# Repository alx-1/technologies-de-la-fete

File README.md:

# technologies-de-la-fete

# The project has moved here : https://gitlab.com/tdlf

ESP32 Ableton Link Midi clock, sensor interface and modular sequencer.

Wiki : https://github.com/alx-1/technologies-de-la-fete/wiki

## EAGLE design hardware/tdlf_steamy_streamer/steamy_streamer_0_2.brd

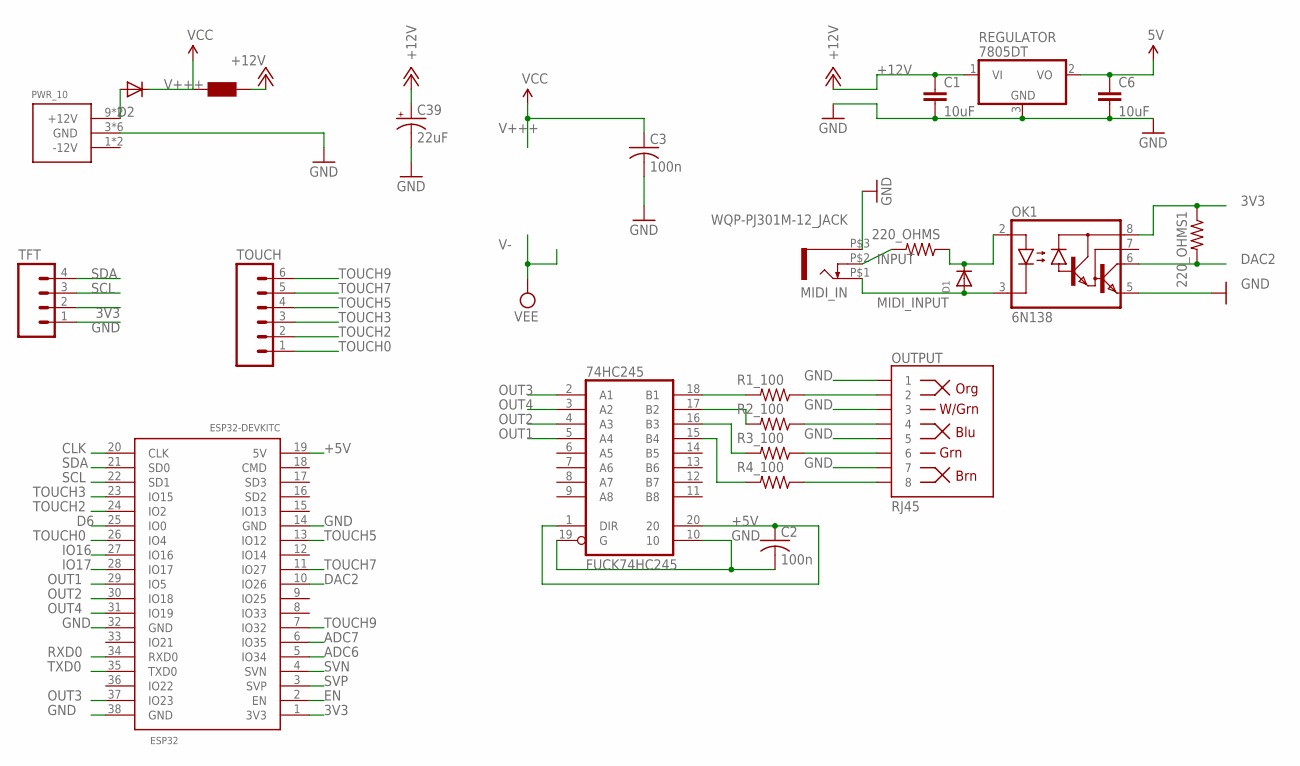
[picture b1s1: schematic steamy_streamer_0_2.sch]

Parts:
74HC245: FUCK74HC245; SO20W
220_OHMS, 220_OHMS1: 1206
C1, C6: 10uF; R1210
C2, C3: 100n; C1206
C39: 22uF; 1206_POL
D1: DIODESMA; SMADIODE
D2: B0450; SOD123
ESP32: ESP32DEVKITC; ESP32-DEVKITC
F1: Würth Electronics 742792664; R0805
MIDI_IN: WQP-PJ301M-12_JACK
OK1: 6N138; DIL08
OUTPUT: RJ45; RJ45-8
PWR_10: POWER_SIMPLE10; POWER_10
R1_100, R2_100, R3_100, R4_100: RESISTOR1206; 1206
REGULATOR: 7805DT; TO252
TFT: M04PTH; 1X04
TOUCH: M06LOCK_LONGPADS; 1X06_LOCK_LONGPADS

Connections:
3V3: 220_OHMS1.1, ESP32.1 (3V3), OK1.8 (VCC), TFT.2
4: OUTPUT.2, R1_100.1
+5V: 74HC245.1 (DIR), 74HC245.20, C2.1, C6.1, ESP32.19 (5V), REGULATOR.2 (VO)
+12V: C1.1, C39.2 (+), F1.1, REGULATOR.1 (VI)
ADC6: ESP32.5 (IO34)
ADC7: ESP32.6 (IO35)
CLK: ESP32.20 (CLK)
D6: ESP32.25 (IO0)
DAC2: 220_OHMS1.2, ESP32.10 (IO26), OK1.6 (VO)
EN: ESP32.2 (EN)
GND: 74HC245.10, 74HC245.19 (G), C1.2, C2.2, C3.2, C6.2, C39.1 (-), ESP32.14 (GND), ESP32.32 (GND), ESP32.38 (GND), MIDI_IN.P$3 (1), OK1.5 (GND), OUTPUT.1, OUTPUT.3, OUTPUT.5, OUTPUT.7, PWR_10.3 (GND), PWR_10.4 (GND), PWR_10.5 (GND), PWR_10.6 (GND), PWR_10.7 (GND), PWR_10.8 (GND), REGULATOR.3 (GND), TFT.1
INPUT: 220_OHMS.2, MIDI_IN.P$2 (3)
IO16: ESP32.27 (IO16)
IO17: ESP32.28 (IO17)
MIDI_INPUT: D1.A, MIDI_IN.P$1 (2), OK1.3 (C)
unnamed: OUTPUT.8, R4_100.1
unnamed: OUTPUT.6, R3_100.1
unnamed: D2.A, PWR_10.9 (+12V), PWR_10.10 (+12V)
unnamed: OUTPUT.4, R2_100.1
unnamed: 220_OHMS.1, D1.C, OK1.2 (A)
unnamed: 74HC245.18 (B1), R1_100.2
unnamed: 74HC245.17 (B2), R2_100.2
unnamed: 74HC245.16 (B3), R3_100.2
unnamed: 74HC245.15 (B4), R4_100.2
OUT1: 74HC245.5 (A4), ESP32.29 (IO5)
OUT2: 74HC245.4 (A3), ESP32.30 (IO18)
OUT3: 74HC245.2 (A1), ESP32.37 (IO23)
OUT4: 74HC245.3 (A2), ESP32.31 (IO19)
RXD0: ESP32.34 (RXD0)
SCL: ESP32.22 (SD1), TFT.3
SDA: ESP32.21 (SD0), TFT.4
SVN: ESP32.4 (SVN)
SVP: ESP32.3 (SVP)
TOUCH0: ESP32.26 (IO4), TOUCH.1
TOUCH2: ESP32.24 (IO2), TOUCH.2
TOUCH3: ESP32.23 (IO15), TOUCH.3
TOUCH5: ESP32.13 (IO12), TOUCH.4
TOUCH7: ESP32.11 (IO27), TOUCH.5
TOUCH9: ESP32.7 (IO32), TOUCH.6
TXD0: ESP32.35 (TXD0)
V+++: C3.1, D2.C, F1.2

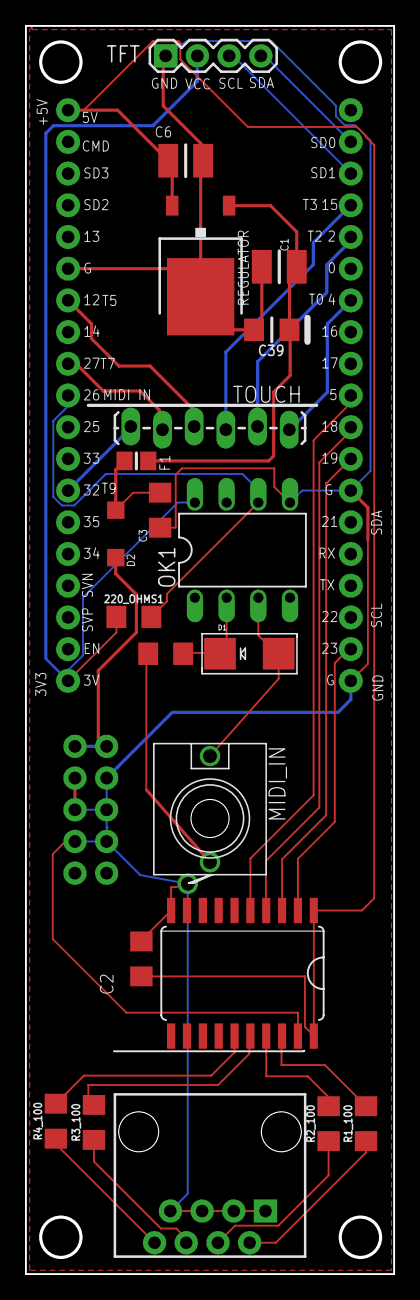
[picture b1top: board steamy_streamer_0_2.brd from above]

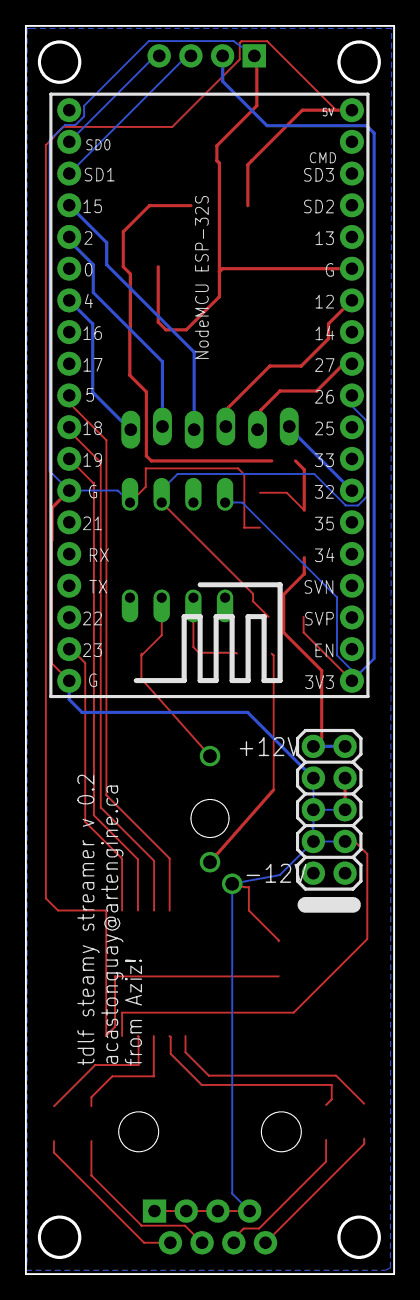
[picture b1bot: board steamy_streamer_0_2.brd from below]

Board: 2 copper layers, 29.5 x 100.0 mm, 23 parts (2 on the bottom side), 30 nets.

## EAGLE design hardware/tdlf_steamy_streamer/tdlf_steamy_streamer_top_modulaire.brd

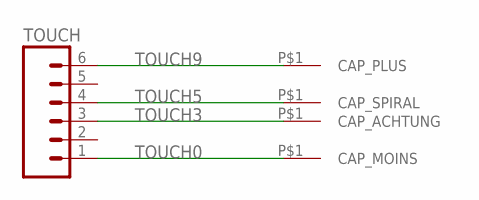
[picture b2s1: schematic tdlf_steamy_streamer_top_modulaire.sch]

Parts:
CAP_PLUS: TDLF_CAP_PLUS
TOUCH: M06SMD-STRAIGHT-COMBO-FEMALE; 1X06_SMD_STRAIGHT_COMBO
U$1: TDLF_CAP_MOINS
U$2: TDLF_CAP_SPIRAL
U$4: TDLF_CAP_ACHTUNG

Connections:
TOUCH0: TOUCH.1, U$1.P$1
TOUCH3: TOUCH.3, U$4.P$1
TOUCH5: TOUCH.4, U$2.P$1
TOUCH9: CAP_PLUS.P$1, TOUCH.6

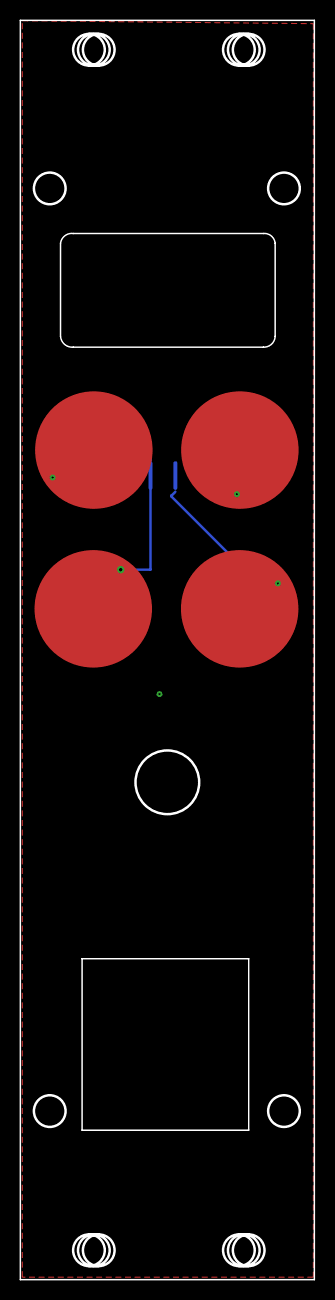
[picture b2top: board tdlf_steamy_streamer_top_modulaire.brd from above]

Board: 2 copper layers, 30.0 x 128.5 mm, 5 parts (1 on the bottom side), 4 nets.

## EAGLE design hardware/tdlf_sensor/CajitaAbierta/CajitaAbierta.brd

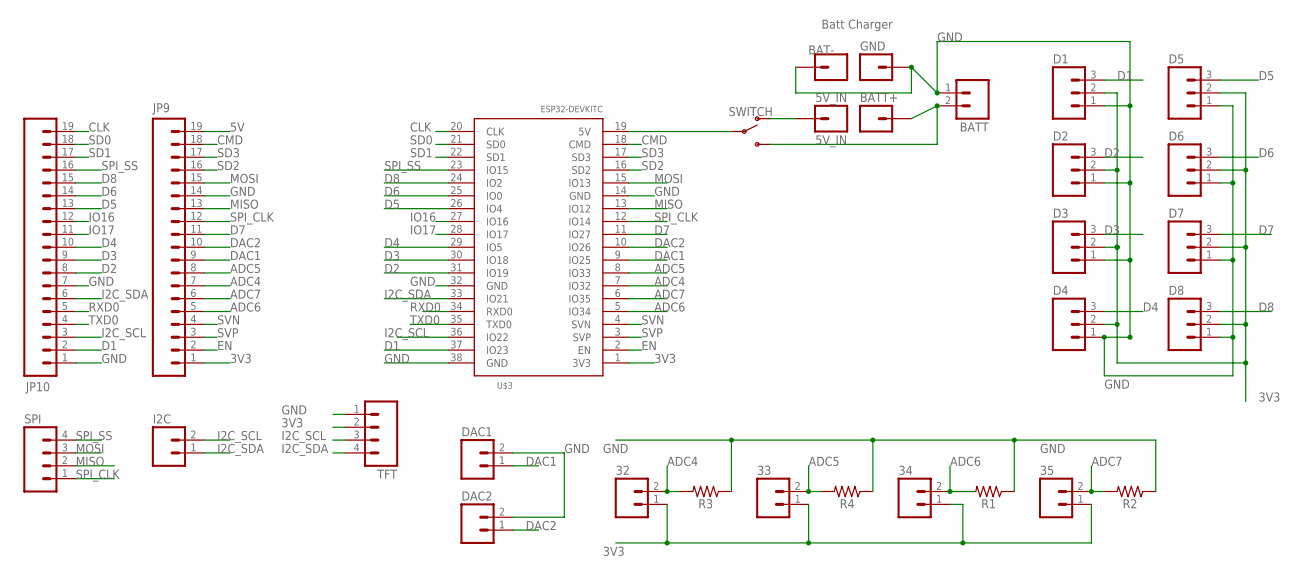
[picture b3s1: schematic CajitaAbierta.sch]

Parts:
5V_IN: 5V_IN; 1X01
32, 33, 34, 35: M02PTH; 1X02
BAT-: M01PTH; 1X01
BATT: M02LOCK_LONGPADS; 1X02_LOCK_LONGPADS
BATT+: M01PTH; 1X01
D1, D2, D3, D4, D5, D6, D7, D8: M03LOCK_LONGPADS; 1X03_LOCK_LONGPADS
DAC1, DAC2: M02PTH; 1X02
GND: Batt Charger; 1X01
I2C: M02PTH; 1X02
JP9, JP10: M191X19; 1X19
R1, R2, R3, R4: 1206
SPI: M04PTH; 1X04
SWITCH: SWITCH-SPDT-SMD-RIGHT-ANGLE; SWITCH_SPST_SMD_A
TFT: M04PTH; 1X04
U$3: ESP32DEVKITC; ESP32-DEVKITC

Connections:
3V3: 32.1, 33.1, 34.1, 35.1, D1.2, D2.2, D3.2, D4.2, D5.2, D6.2, D7.2, D8.2, JP9.1, TFT.2, U$3.1 (3V3)
5V: JP9.19, SWITCH.2, U$3.19 (5V)
5V_IN: 5V_IN.1, SWITCH.1 (O)
ADC4: 32.2, JP9.7, R3.2, U$3.7 (IO32)
ADC5: 33.2, JP9.8, R4.2, U$3.8 (IO33)
ADC6: 34.2, JP9.5, R1.2, U$3.5 (IO34)
ADC7: 35.2, JP9.6, R2.2, U$3.6 (IO35)
BATT+: BATT.2, BATT+.1, SWITCH.3 (S)
CLK: JP10.19, U$3.20 (CLK)
CMD: JP9.18, U$3.18 (CMD)
D1: D1.3, JP10.2, U$3.37 (IO23)
D2: D2.3, JP10.8, U$3.31 (IO19)
D3: D3.3, JP10.9, U$3.30 (IO18)
D4: D4.3, JP10.10, U$3.29 (IO5)
D5: D5.3, JP10.13, U$3.26 (IO4)
D6: D6.3, JP10.14, U$3.25 (IO0)
D7: D7.3, JP9.11, U$3.11 (IO27)
D8: D8.3, JP10.15, U$3.24 (IO2)
DAC1: DAC1.1, JP9.9, U$3.9 (IO25)
DAC2: DAC2.1, JP9.10, U$3.10 (IO26)
EN: JP9.2, U$3.2 (EN)
GND: BAT-.1, BATT.1, D1.1, D2.1, D3.1, D4.1, D5.1, D6.1, D7.1, D8.1, DAC1.2, DAC2.2, GND.1, JP9.14, JP10.1, JP10.7, R1.1, R2.1, R3.1, R4.1, TFT.1, U$3.14 (GND), U$3.32 (GND), U$3.38 (GND)
I2C_SCL: I2C.2, JP10.3, TFT.3, U$3.36 (IO22)
I2C_SDA: I2C.1, JP10.6, TFT.4, U$3.33 (IO21)
IO16: JP10.12, U$3.27 (IO16)
IO17: JP10.11, U$3.28 (IO17)
MISO: JP9.13, SPI.2, U$3.13 (IO12)
MOSI: JP9.15, SPI.3, U$3.15 (IO13)
RXD0: JP10.5, U$3.34 (RXD0)
SD0: JP10.18, U$3.21 (SD0)
SD1: JP10.17, U$3.22 (SD1)
SD2: JP9.16, U$3.16 (SD2)
SD3: JP9.17, U$3.17 (SD3)
SPI_CLK: JP9.12, SPI.1, U$3.12 (IO14)
SPI_SS: JP10.16, SPI.4, U$3.23 (IO15)
SVN: JP9.4, U$3.4 (SVN)
SVP: JP9.3, U$3.3 (SVP)
TXD0: JP10.4, U$3.35 (TXD0)

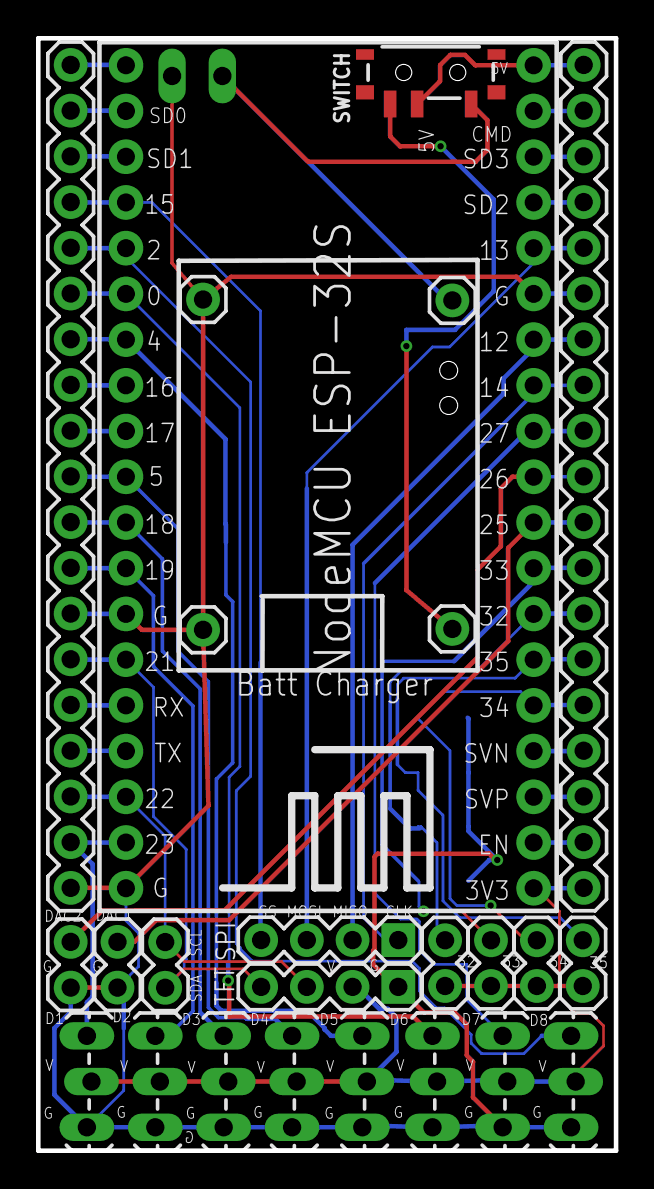
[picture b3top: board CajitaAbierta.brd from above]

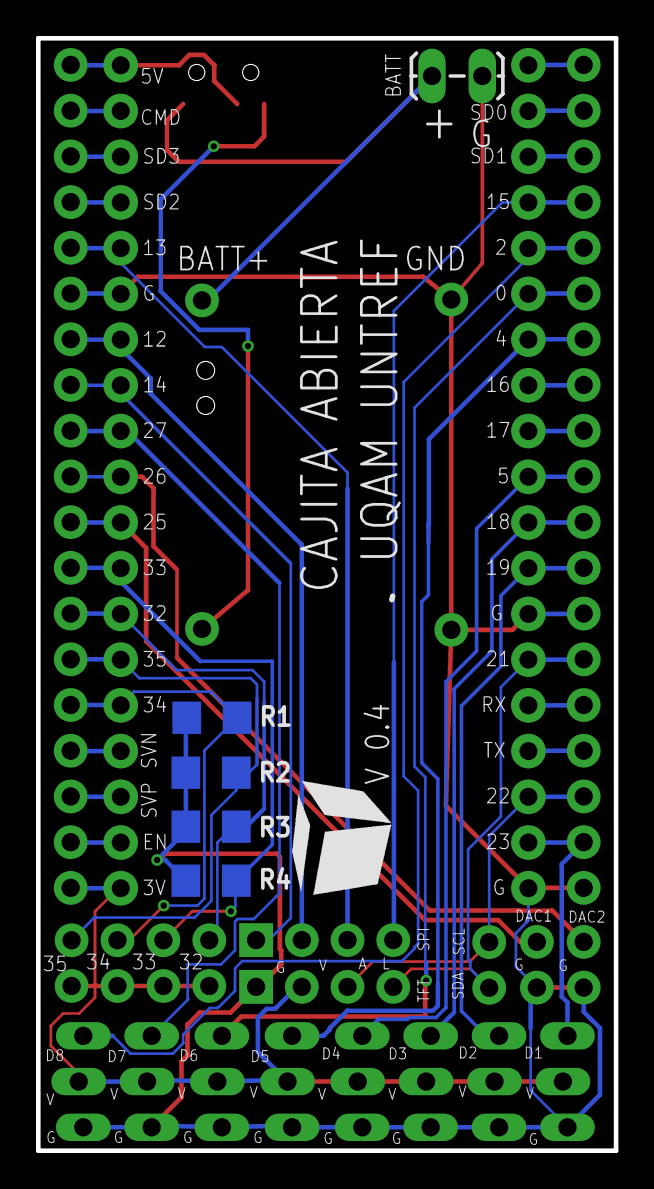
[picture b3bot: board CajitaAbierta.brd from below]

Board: 2 copper layers, 32.1 x 61.8 mm, 30 parts (5 on the bottom side), 38 nets.

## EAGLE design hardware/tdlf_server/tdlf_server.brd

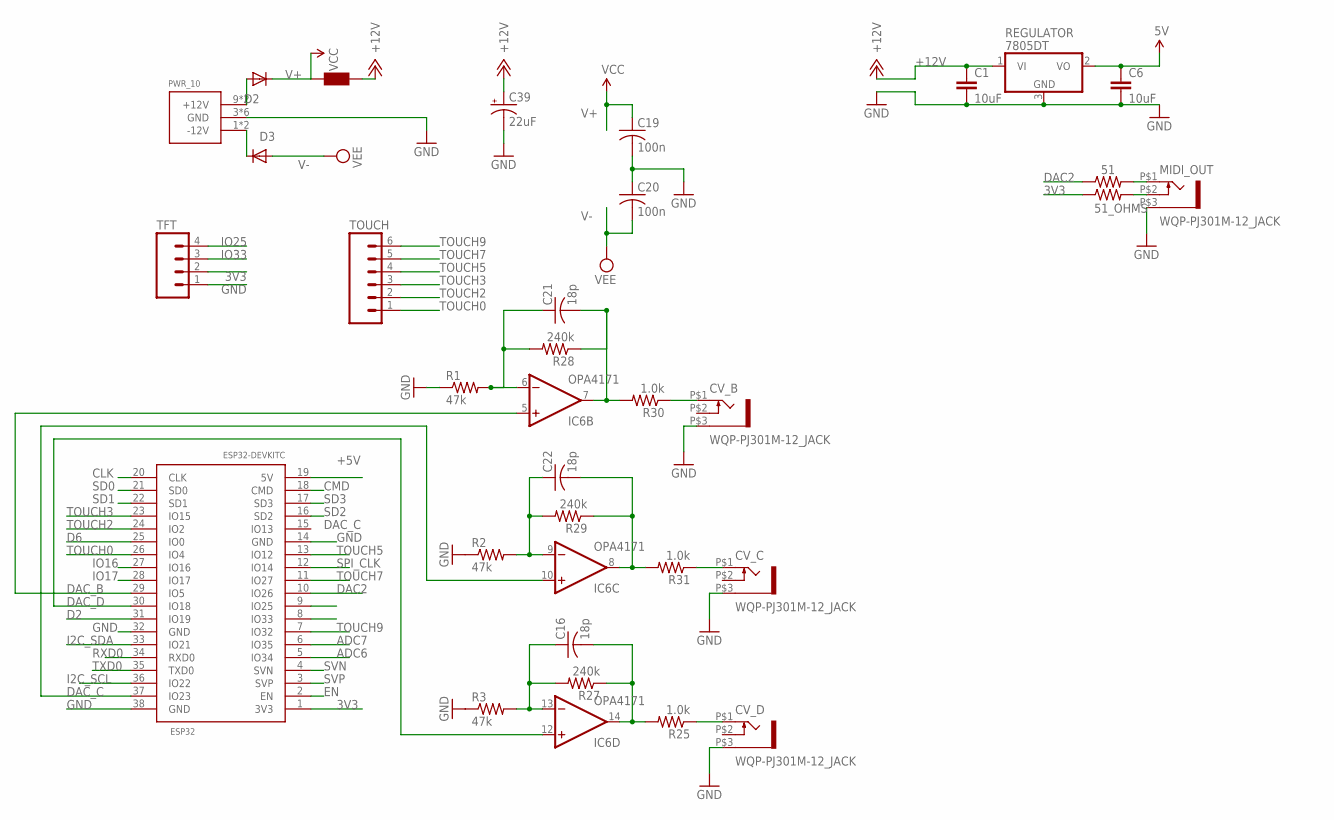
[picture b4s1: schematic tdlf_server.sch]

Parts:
51, 51_OHMS: 1206
C1, C6: 10uF; R1210
C16, C21, C22: 18p; C0603
C19, C20: 100n; C0603
C39: 22uF; 1206_POL
CV_B: WQP-PJ301M-12_JACK
CV_C: WQP-PJ301M-12_JACK
CV_D: WQP-PJ301M-12_JACK
D2: B0450; SOD123
D3: B0540; SOD123
ESP32: ESP32DEVKITC; ESP32-DEVKITC
F1: Würth Electronics 742792664; R0805
IC6: OPA4171; SO14
MIDI_OUT: WQP-PJ301M-12_JACK
PWR_10: POWER_SIMPLE10; POWER_10
R1, R2, R3: 47k; R1206
R25, R30, R31: 1.0k; R0603
R27, R28, R29: 240k; R0603
REGULATOR: 7805DT; TO252
TFT: M04PTH; 1X04
TOUCH: M06LOCK_LONGPADS; 1X06_LOCK_LONGPADS

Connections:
3V: 51_OHMS.2, MIDI_OUT.P$2 (3)
3V3: 51_OHMS.1, ESP32.1 (3V3), TFT.2
+5V: C6.1, ESP32.19 (5V), REGULATOR.2 (VO)
+12V: C1.1, C39.2 (+), F1.1, REGULATOR.1 (VI)
ADC6: ESP32.5 (IO34)
ADC7: ESP32.6 (IO35)
CLK: ESP32.20 (CLK)
CMD: ESP32.18 (CMD)
D2: ESP32.31 (IO19)
D6: ESP32.25 (IO0)
DAC2: 51.1, ESP32.10 (IO26)
DAC_B: ESP32.29 (IO5), IC6.5 (+IN)
DAC_C: ESP32.37 (IO23), IC6.10 (+IN)
DAC_D: ESP32.30 (IO18), IC6.12 (+IN)
EN: ESP32.2 (EN)
GND: C1.2, C6.2, C19.2, C20.1, C39.1 (-), CV_B.P$3 (1), CV_C.P$3 (1), CV_D.P$3 (1), ESP32.14 (GND), ESP32.32 (GND), ESP32.38 (GND), MIDI_OUT.P$3 (1), PWR_10.3 (GND), PWR_10.4 (GND), PWR_10.5 (GND), PWR_10.6 (GND), PWR_10.7 (GND), PWR_10.8 (GND), R1.1, R2.1, R3.1, REGULATOR.3 (GND), TFT.1
I2C_SCL: ESP32.36 (IO22)
I2C_SDA: ESP32.33 (IO21)
IO16: ESP32.27 (IO16)
IO17: ESP32.28 (IO17)
IO25: ESP32.9 (IO25), TFT.4
IO33: ESP32.8 (IO33), TFT.3
unnamed: D3.C, PWR_10.1 (-12V), PWR_10.2 (-12V)
unnamed: C22.1, IC6.9 (-IN), R2.2, R29.2
unnamed: CV_C.P$1 (2), R31.1
unnamed: D2.A, PWR_10.9 (+12V), PWR_10.10 (+12V)
unnamed: CV_D.P$1 (2), R25.1
unnamed: C21.2, IC6.7 (OUT), R28.1, R30.2
unnamed: C22.2, IC6.8 (OUT), R29.1, R31.2
unnamed: C16.2, IC6.14 (OUT), R25.2, R27.1
unnamed: C16.1, IC6.13 (-IN), R3.2, R27.2
unnamed: C21.1, IC6.6 (-IN), R1.2, R28.2
unnamed: CV_B.P$1 (2), R30.1
PIN27: 51.2, MIDI_OUT.P$1 (2)
RXD0: ESP32.34 (RXD0)
SD0: ESP32.21 (SD0)
SD1: ESP32.22 (SD1)
SD2: ESP32.16 (SD2)
SD3: ESP32.17 (SD3)
SPI_CLK: ESP32.12 (IO14)
SVN: ESP32.4 (SVN)
SVP: ESP32.3 (SVP)
TOUCH0: ESP32.26 (IO4), TOUCH.1
TOUCH2: ESP32.24 (IO2), TOUCH.2
TOUCH3: ESP32.23 (IO15), TOUCH.3
TOUCH5: ESP32.13 (IO12), TOUCH.4
TOUCH7: ESP32.11 (IO27), TOUCH.5
TOUCH9: ESP32.7 (IO32), TOUCH.6
TXD0: ESP32.35 (TXD0)
V+: C19.1, D2.C, F1.2, IC6.4 (V+)
V-: C20.2, D3.A, IC6.11 (V-)

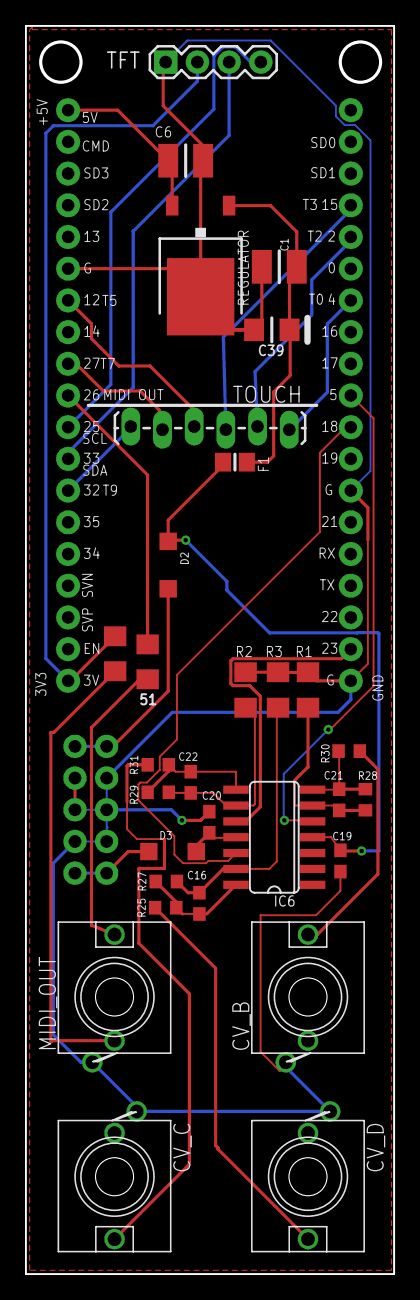
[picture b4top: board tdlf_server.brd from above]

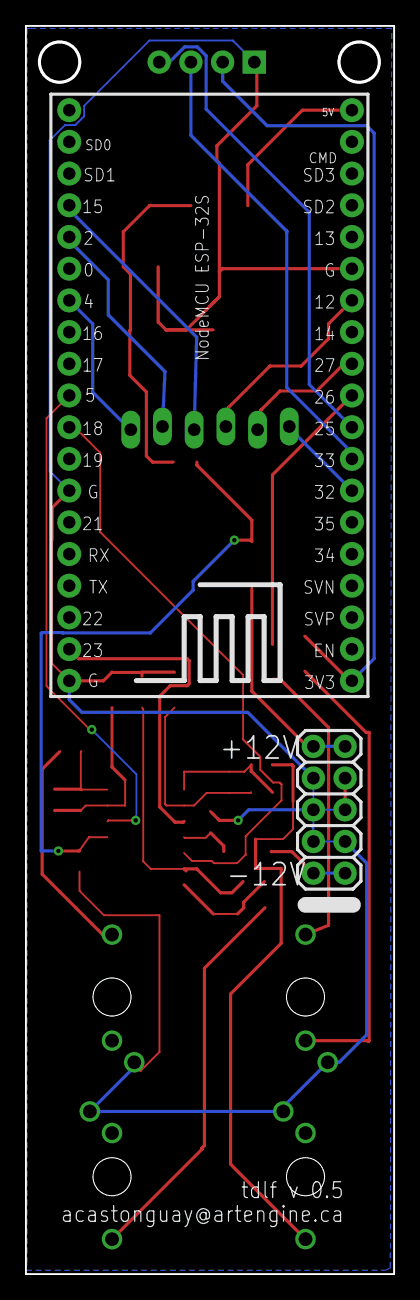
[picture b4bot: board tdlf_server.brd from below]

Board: 2 copper layers, 29.5 x 100.0 mm, 32 parts (2 on the bottom side), 31 nets.

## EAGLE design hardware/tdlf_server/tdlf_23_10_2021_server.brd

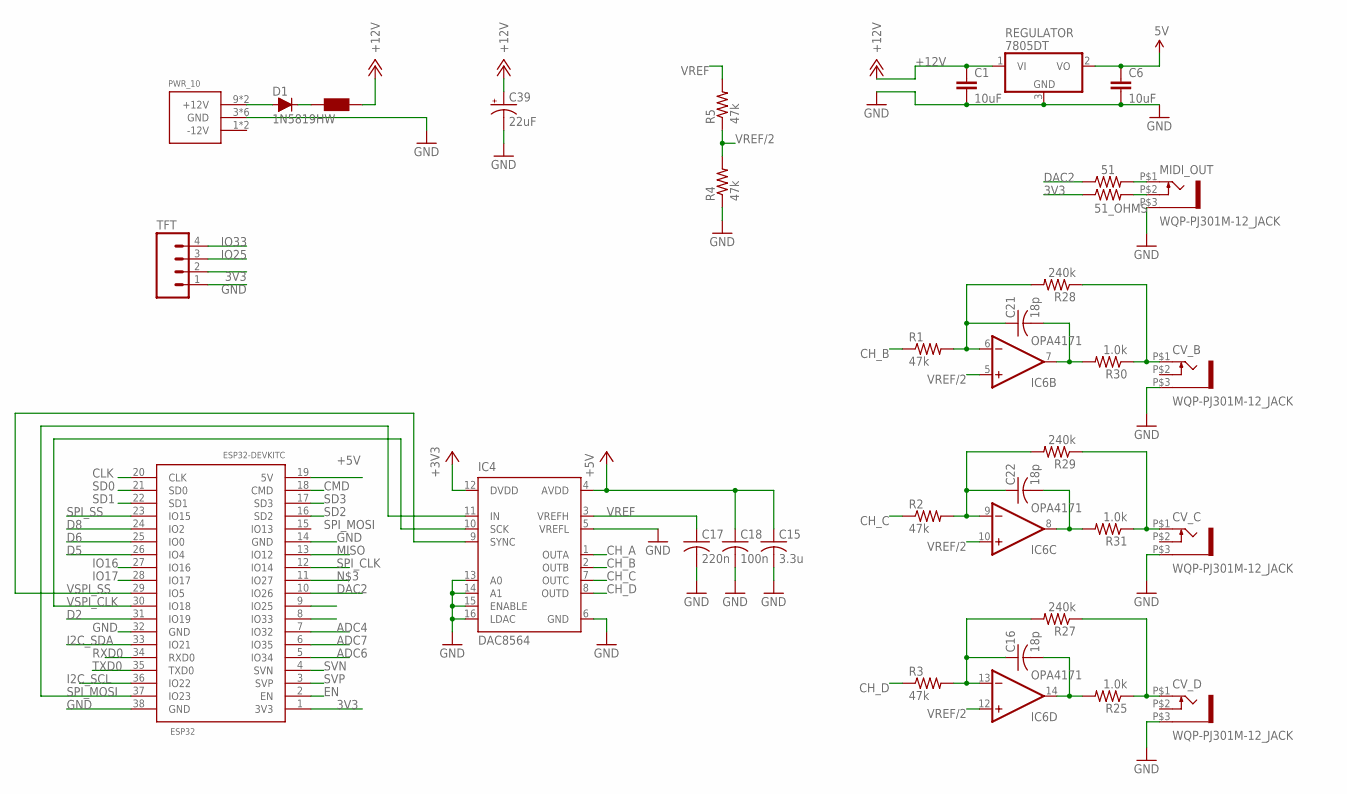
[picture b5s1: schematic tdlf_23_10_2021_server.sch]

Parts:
51, 51_OHMS: 1206
C1, C6: 10uF; R1210
C15: 3.3u; C0603
C16, C21, C22: 18p; C0603
C17: 220n; C0603
C18: 100n; C0603
C39: 22uF; 1206_POL
CV_B: WQP-PJ301M-12_JACK
CV_C: WQP-PJ301M-12_JACK
CV_D: WQP-PJ301M-12_JACK
D1: 1N5819HW; SOD123
ESP32: ESP32DEVKITC; ESP32-DEVKITC
F1: Würth Electronics 742792664; R0805
IC4: DAC8564; SOP65P640X110-16N
IC6: OPA4171; SO14
MIDI_OUT: WQP-PJ301M-12_JACK
PWR_10: POWER_SIMPLE10; POWER_10
R1, R2, R3, R4, R5: 47k; R1206
R25, R30, R31: 1.0k; R0603
R27, R28, R29: 240k; R0603
REGULATOR: 7805DT; TO252
TFT: M04PTH; 1X04

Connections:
3V: 51_OHMS.2, MIDI_OUT.P$2 (3)
3V3: 51_OHMS.1, ESP32.1 (3V3), TFT.2
+3V3: IC4.12 (DVDD)
+5V: C6.1, C15.1, C18.1, ESP32.19 (5V), IC4.4 (AVDD), REGULATOR.2 (VO)
+12: D1.+, PWR_10.9 (+12V), PWR_10.10 (+12V)
+12V: C1.1, C39.2 (+), F1.1, REGULATOR.1 (VI)
ADC4: ESP32.7 (IO32)
ADC6: ESP32.5 (IO34)
ADC7: ESP32.6 (IO35)
CH_A: IC4.1 (OUTA)
CH_B: IC4.2 (OUTB), R1.1
CH_C: IC4.7 (OUTC), R2.1
CH_D: IC4.8 (OUTD), R3.1
CLK: ESP32.20 (CLK)
CMD: ESP32.18 (CMD)
D2: ESP32.31 (IO19)
D5: ESP32.26 (IO4)
D6: ESP32.25 (IO0)
D8: ESP32.24 (IO2)
DAC2: 51.1, ESP32.10 (IO26)
EN: ESP32.2 (EN)
GND: C1.2, C6.2, C15.2, C17.2, C18.2, C39.1 (-), CV_B.P$3 (1), CV_C.P$3 (1), CV_D.P$3 (1), ESP32.14 (GND), ESP32.32 (GND), ESP32.38 (GND), IC4.5 (VREFL), IC4.6 (GND), IC4.13 (A0), IC4.14 (A1), IC4.15 (ENABLE), IC4.16 (LDAC), MIDI_OUT.P$3 (1), PWR_10.3 (GND), PWR_10.4 (GND), PWR_10.5 (GND), PWR_10.6 (GND), PWR_10.7 (GND), PWR_10.8 (GND), R4.1, REGULATOR.3 (GND), TFT.1
I2C_SCL: ESP32.36 (IO22)
I2C_SDA: ESP32.33 (IO21)
IO16: ESP32.27 (IO16)
IO17: ESP32.28 (IO17)
IO25: ESP32.9 (IO25), TFT.3
IO33: ESP32.8 (IO33), TFT.4
MISO: ESP32.13 (IO12)
unnamed: C22.1, IC6.9 (-IN), R2.2, R29.2
unnamed: D1.-, F1.2
unnamed: C21.2, IC6.7 (OUT), R30.2
unnamed: C22.2, IC6.8 (OUT), R31.2
unnamed: C16.2, IC6.14 (OUT), R25.2
unnamed: CV_C.P$1 (2), R29.1, R31.1
unnamed: CV_D.P$1 (2), R25.1, R27.1
unnamed: C16.1, IC6.13 (-IN), R3.2, R27.2
unnamed: C21.1, IC6.6 (-IN), R1.2, R28.2
unnamed: CV_B.P$1 (2), R28.1, R30.1
PIN27: 51.2, MIDI_OUT.P$1 (2)
RXD0: ESP32.34 (RXD0)
SD0: ESP32.21 (SD0)
SD1: ESP32.22 (SD1)
SD2: ESP32.16 (SD2)
SD3: ESP32.17 (SD3)
SPI_CLK: ESP32.12 (IO14)
SPI_MOSI: ESP32.37 (IO23), IC4.11 (IN)
SPI_SS: ESP32.23 (IO15)
SVN: ESP32.4 (SVN)
SVP: ESP32.3 (SVP)
TXD0: ESP32.35 (TXD0)
V+: IC6.4 (V+)
V-: IC6.11 (V-)
VREF: C17.1, IC4.3 (VREFH), R5.2
VREF/2: IC6.5 (+IN), IC6.10 (+IN), IC6.12 (+IN), R4.2, R5.1
VSPI_CLK: ESP32.30 (IO18), IC4.10 (SCK)
VSPI_SS: ESP32.29 (IO5), IC4.9 (SYNC)

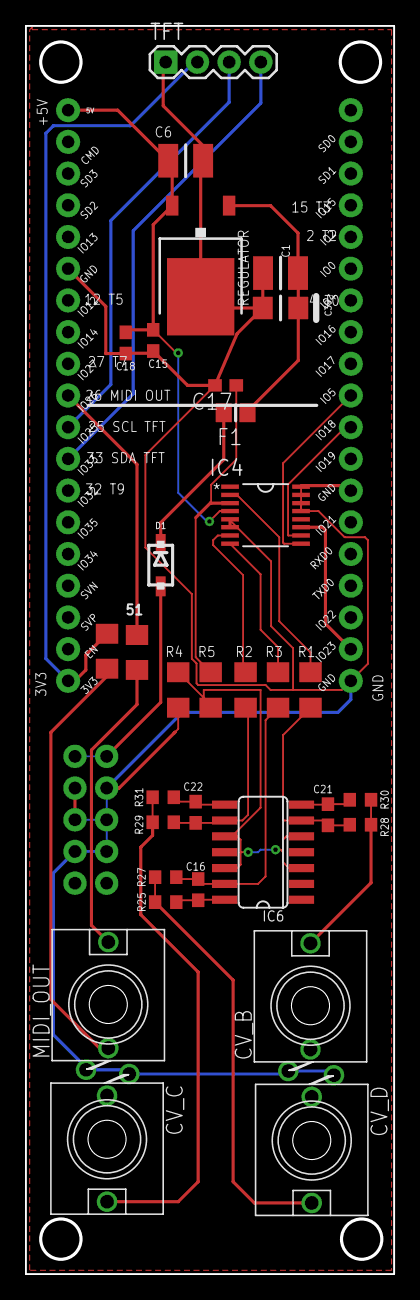
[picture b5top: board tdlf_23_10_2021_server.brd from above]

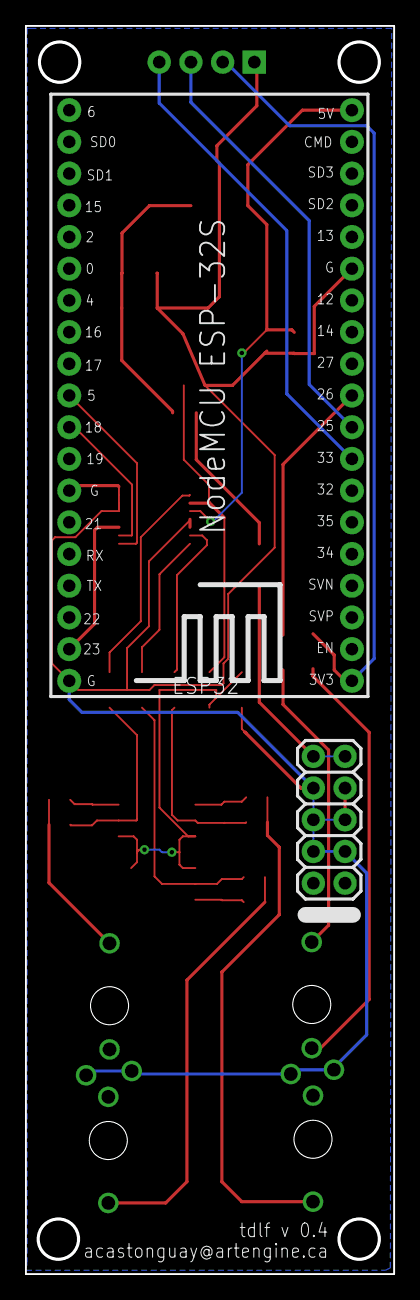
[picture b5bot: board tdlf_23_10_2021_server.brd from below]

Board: 2 copper layers, 29.5 x 100.0 mm, 34 parts (2 on the bottom side), 28 nets.

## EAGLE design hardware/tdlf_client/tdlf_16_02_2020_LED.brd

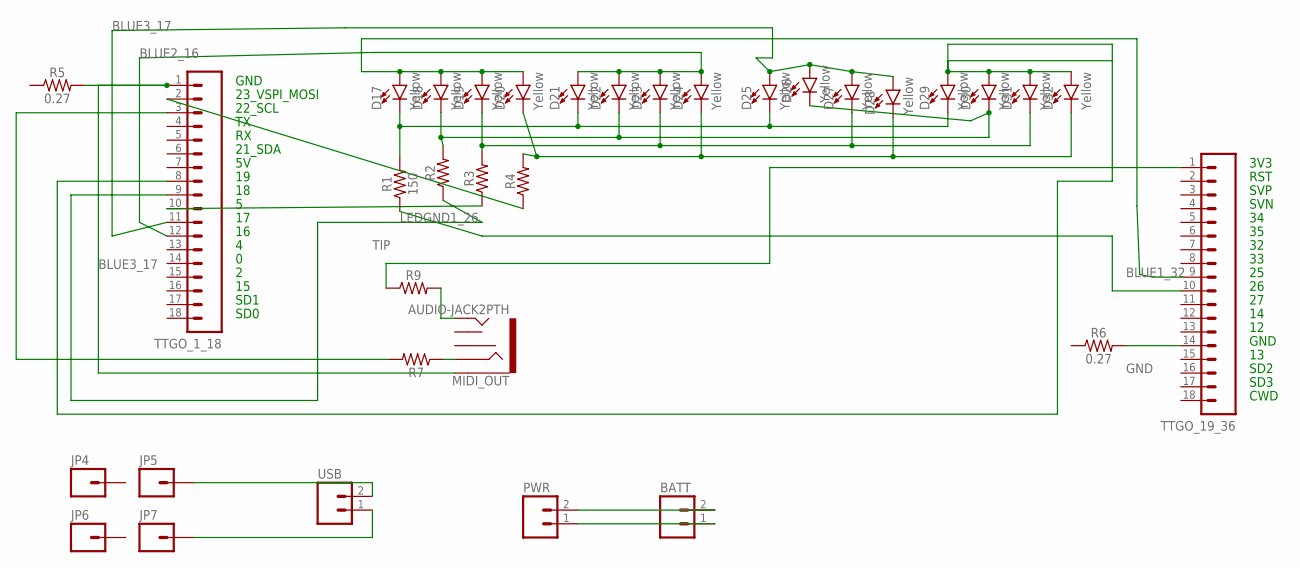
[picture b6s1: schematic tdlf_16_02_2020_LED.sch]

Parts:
BATT: M02PTH; 1X02
D17, D18, D19, D20, D21, D22, D23, D24, D25, D26, D27, D28, D29, D30, D31, D32: Yellow; LED-1206
JP4, JP5, JP6, JP7: M01PTH; 1X01
MIDI_OUT: AUDIO-JACK2PTH; AUDIO-JACK
PWR: M02PTH; 1X02
R1: 150; 1206
R2, R3, R4, R7, R9: 1206
R5, R6: 0.27; 0603
TTGO_1_18, TTGO_19_36: M18_; 1X18
USB: M02PTH; 1X02

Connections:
3.3V: R9.1, TTGO_19_36.1
BLUE1_32: D17.A, D18.A, D19.A, D20.A, TTGO_19_36.9
BLUE2_16: D21.A, D22.A, D23.A, D24.A, TTGO_1_18.12
BLUE3_17: D25.A, D26.A, D27.A, D28.A, TTGO_1_18.11
BLUE4_34: D29.A, D30.A, D31.A, D32.A, TTGO_1_18.8
GND: MIDI_OUT.SLEEVE, R5.2, R6.2, TTGO_1_18.1, TTGO_19_36.14
LEDGND1_26: R1.1, TTGO_19_36.10
LEDGND2_SVP: R2.1, TTGO_1_18.9
LEDGND3_5_VSPI_SS: R3.1, TTGO_1_18.10
LEDGND4_23: R4.1, TTGO_1_18.2
MIDI_DATA: R7.2, TTGO_1_18.3
unnamed: D17.C, D21.C, D25.C, D29.C, R1.2
unnamed: D18.C, D22.C, D26.C, D30.C, R2.2
unnamed: D19.C, D23.C, D27.C, D31.C, R3.2
unnamed: D20.C, D24.C, D28.C, D32.C, R4.2
unnamed: JP5.1, USB.2
unnamed: JP7.1, USB.1
unnamed: BATT.2, PWR.2
unnamed: BATT.1, PWR.1
RING: MIDI_OUT.RING, R7.1
TIP: MIDI_OUT.TIP, R9.2

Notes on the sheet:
3V3
RST
SVP
SVN
GND
SD2
SD3
CWD
23_VSPI_MOSI
22_SCL
21_SDA
SD1
SD0

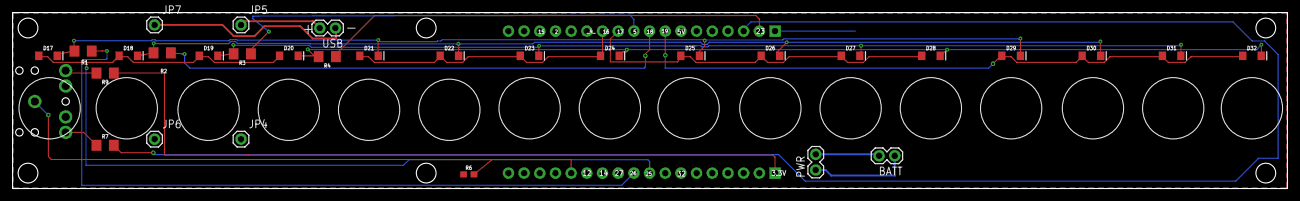
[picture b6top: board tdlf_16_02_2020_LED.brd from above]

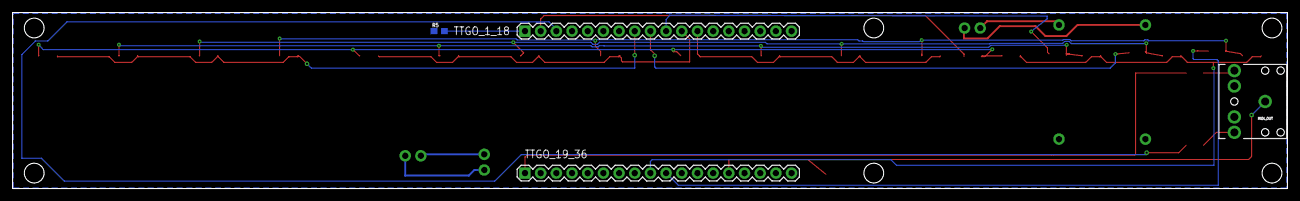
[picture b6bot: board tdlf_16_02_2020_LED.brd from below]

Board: 2 copper layers, 206.5 x 28.5 mm, 34 parts (4 on the bottom side), 21 nets.

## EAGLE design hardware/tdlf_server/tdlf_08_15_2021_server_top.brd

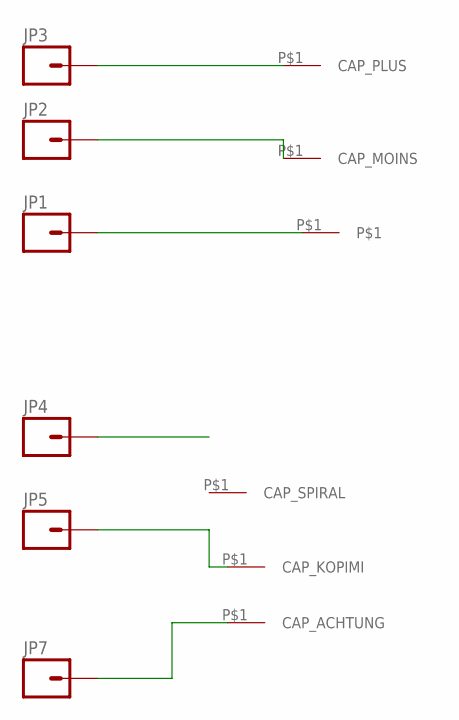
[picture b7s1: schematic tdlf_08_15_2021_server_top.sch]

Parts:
CAP_MUSH: MUSH; TDLF_CAP_02
CAP_PLUS: TDLF_CAP_PLUS
JP1, JP2, JP3, JP4, JP5, JP7: M01SMD; LUXEON-PAD
U$1: TDLF_CAP_MOINS
U$2: TDLF_CAP_SPIRAL
U$3: TDLF_CAP_KOPIMI
U$4: TDLF_CAP_ACHTUNG

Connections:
CHAMPI: CAP_MUSH.P$1, JP1.P$1
KOPIMI: JP5.P$1, U$3.P$1
MOINS: JP2.P$1, U$1.P$1
unnamed: JP7.P$1, U$4.P$1
PLUS: CAP_PLUS.P$1, JP3.P$1
SPIRAL: JP4.P$1

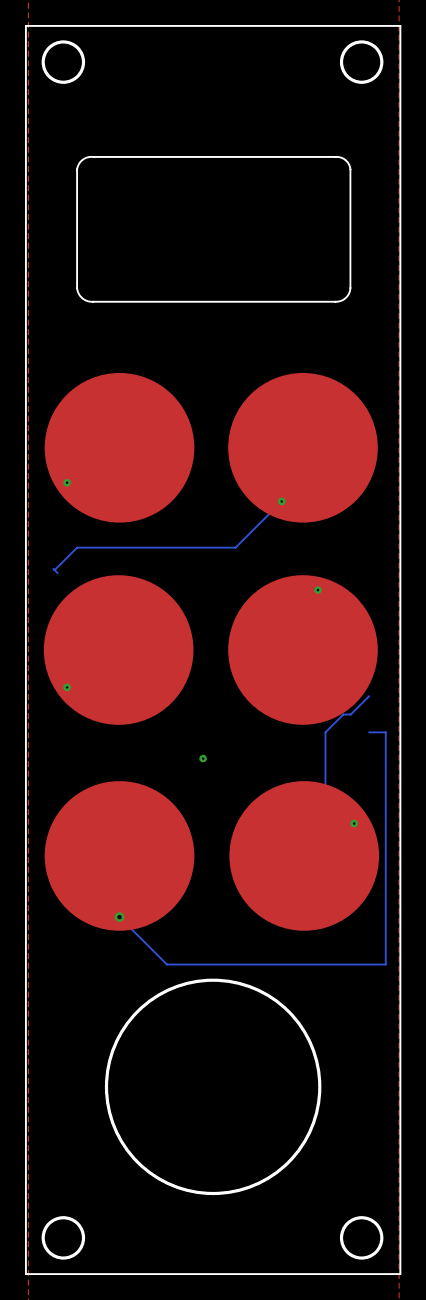
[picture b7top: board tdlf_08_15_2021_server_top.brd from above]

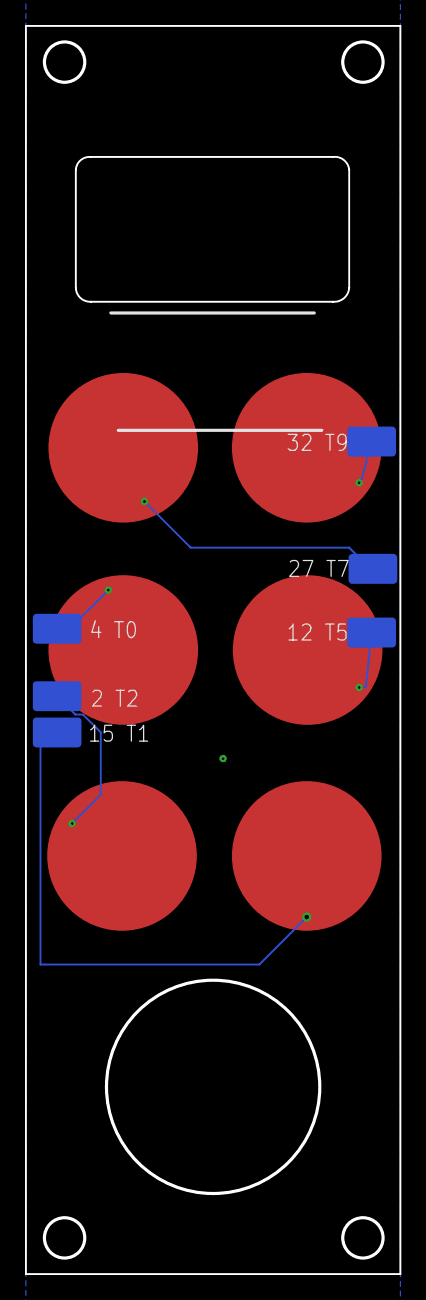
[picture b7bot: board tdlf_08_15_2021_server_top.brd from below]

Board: 2 copper layers, 30.0 x 100.0 mm, 12 parts (6 on the bottom side), 5 nets.

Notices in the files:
parts and their libraries:
SparkFun-LED: Licensing: Creative Commons ShareAlike 4.0 International - https://creativecommons.org/licenses/by-sa/4.0
